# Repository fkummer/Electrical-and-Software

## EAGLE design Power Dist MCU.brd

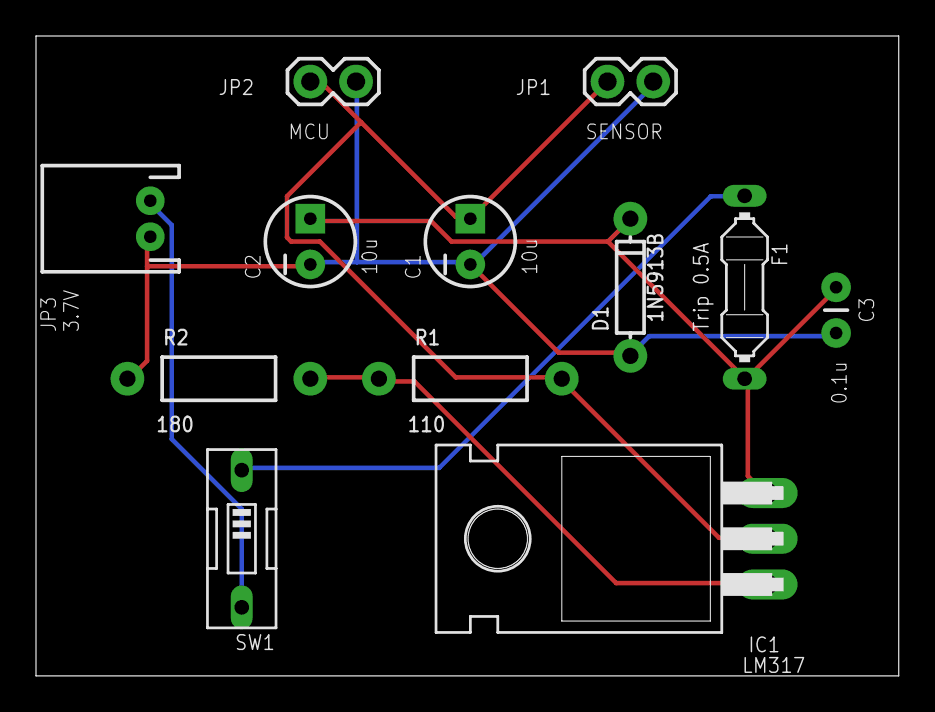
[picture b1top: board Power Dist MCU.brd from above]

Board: 2 copper layers, 47.9 x 35.5 mm, 12 parts (0 on the bottom side), 6 nets.

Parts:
C1, C2: 10u; CPOL-RADIAL-10UF-25V
C3: 0.1u; CAP-PTH-SMALL
D1: 1N5913B; DIODE-BZT52
F1: Trip 0.5A; PICOFUSE
IC1: LM317; TO220H
JP1: SENSOR; 1X02
JP2: MCU; 1X02
JP3: 3.7V; JST-2-PTH
R1: 110; AXIAL-0.4
R2: 180; AXIAL-0.4
SW1: EDG-01

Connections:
GND: C1.2, C2.2, C3.2, D1.A, JP1.2, JP2.2, JP3.1, R2.P$1
unnamed: F1.1, SW1.1
unnamed: JP3.2, SW1.2
unnamed: IC1.1, R1.P$1, R2.P$2
unnamed: C2.1, C3.1, D1.C, F1.2, IC1.3
VOUT: C1.1, IC1.2, JP1.1, JP2.1, R1.P$2

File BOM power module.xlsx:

Part Name | Value | Quantity | Datasheet | Supplier | Notes
LM317 Voltage Regulator | 1.5A current MAX | 1 | http://cdn.sparkfun.com/datasheets/Components/General/LM317TG.pdf | https://www.sparkfun.com/products/527 | MCU
LM350 | 3A+ | 1 | http://www.ti.com/lit/ds/symlink/lm350a.pdf | https://www.arrow.com/en/products/lm350t/texas-instruments?g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 | Motor
TVS DIODE 5VWM 9.2VC DO204AC | 6.4V Breakdown | 1 | http://www.littelfuse.com/~/media/electronics/datasheets/tvs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 | http://www.digikey.com/product-detail/en/littelfuse-inc/SA5.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 | Motor
Lithium Ion Battery | 2000mAh 2C 3.7V | 1 | https://www.sparkfun.com/datasheets/Batteries/UnionBattery-2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 | https://www.sparkfun.com/products/8483 | MCU
LiPo Battery JST Connector | 450mAh 25C 7.4V | 1 | http://www.buddyrc.com/glacier-20c-450mah-2s-jst.html | http://www.buddyrc.com/glacier-20c-450mah-2s-jst.html | Motor
Zener Diode | 3.3V impedence | 1 | http://www.mouser.com/ProductDetail/ON-Semiconductor/1N5913B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 | http://www.mouser.com/ds/2/308/1N5913B-D-11179.pdf | MCU
PTC Fuse | 3A hold 6A trip | 1 | http://www.littelfuse.com/~/media/electronics/product_specif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 | http://www.digikey.com/product-detail/en/RXEF300/RXEF300HF-N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

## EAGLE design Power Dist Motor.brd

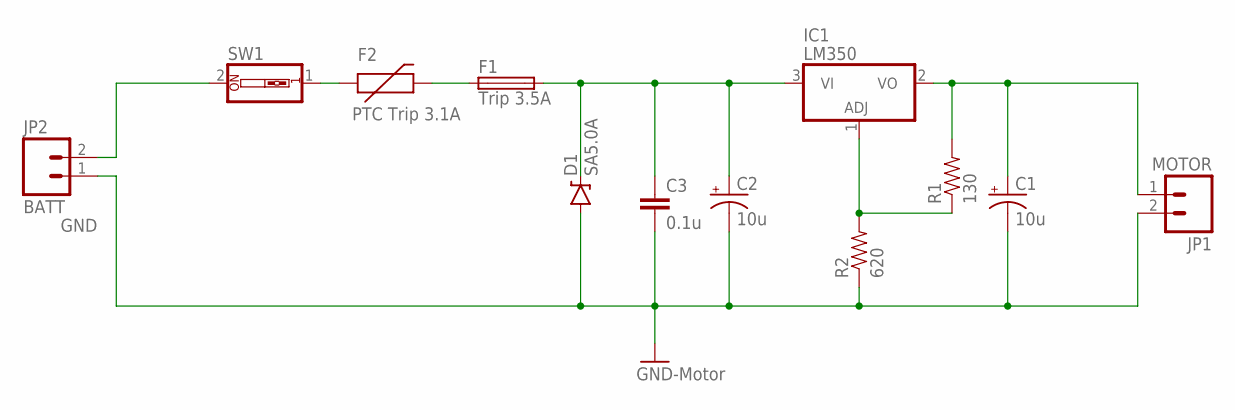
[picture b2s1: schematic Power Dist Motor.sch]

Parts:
C1, C2: 10u; CPOL-RADIAL-10UF-25V
C3: 0.1u; CAP-PTH-SMALL
D1: SA5.0A; DIODE-BZT52
F1: Trip 3.5A; PICOFUSE
F2: PTC Trip 3.1A; PTC
IC1: LM350; TO220H
JP1: MOTOR; 1X02
JP2: BATT; 1X02
R1: 130; AXIAL-0.4
R2: 620; AXIAL-0.4
SW1: SW_DIP-1; EDG-01

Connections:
GND: C1.2 (-), C2.2 (-), C3.2, D1.A, JP1.2, JP2.1, R2.P$1 (1)
unnamed: C1.1 (+), IC1.2 (VO), JP1.1, R1.P$2 (2)
unnamed: JP2.2, SW1.2
unnamed: F2.P$1 (1), SW1.1
unnamed: IC1.1 (ADJ), R1.P$1 (1), R2.P$2 (2)
unnamed: F1.1, F2.P$2 (2)
unnamed: C2.1 (+), C3.1, D1.C, F1.2, IC1.3 (VI)

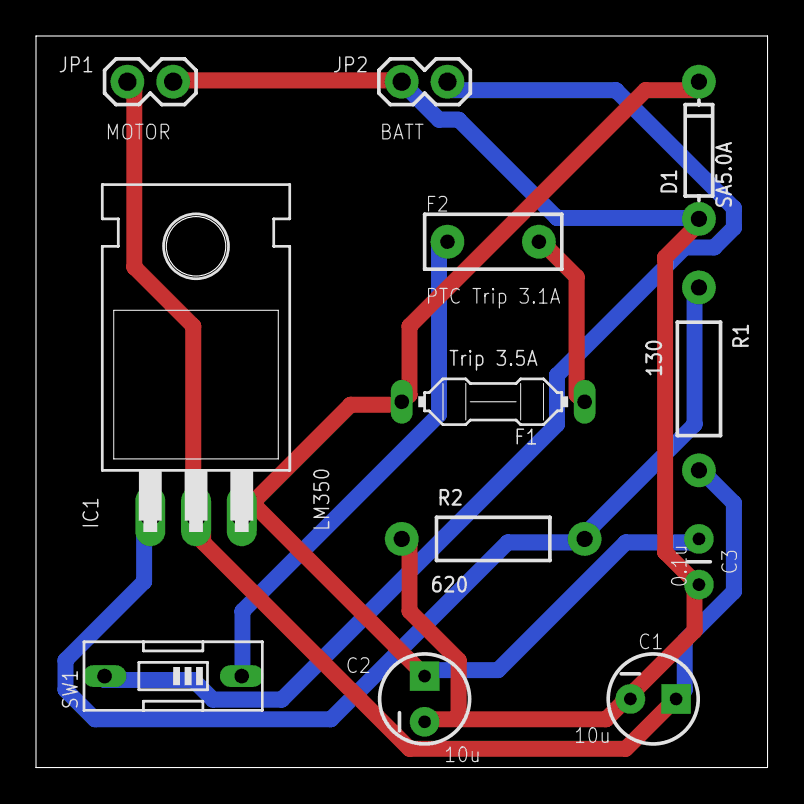
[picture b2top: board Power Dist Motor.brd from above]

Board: 2 copper layers, 40.6 x 40.6 mm, 12 parts (0 on the bottom side), 7 nets.

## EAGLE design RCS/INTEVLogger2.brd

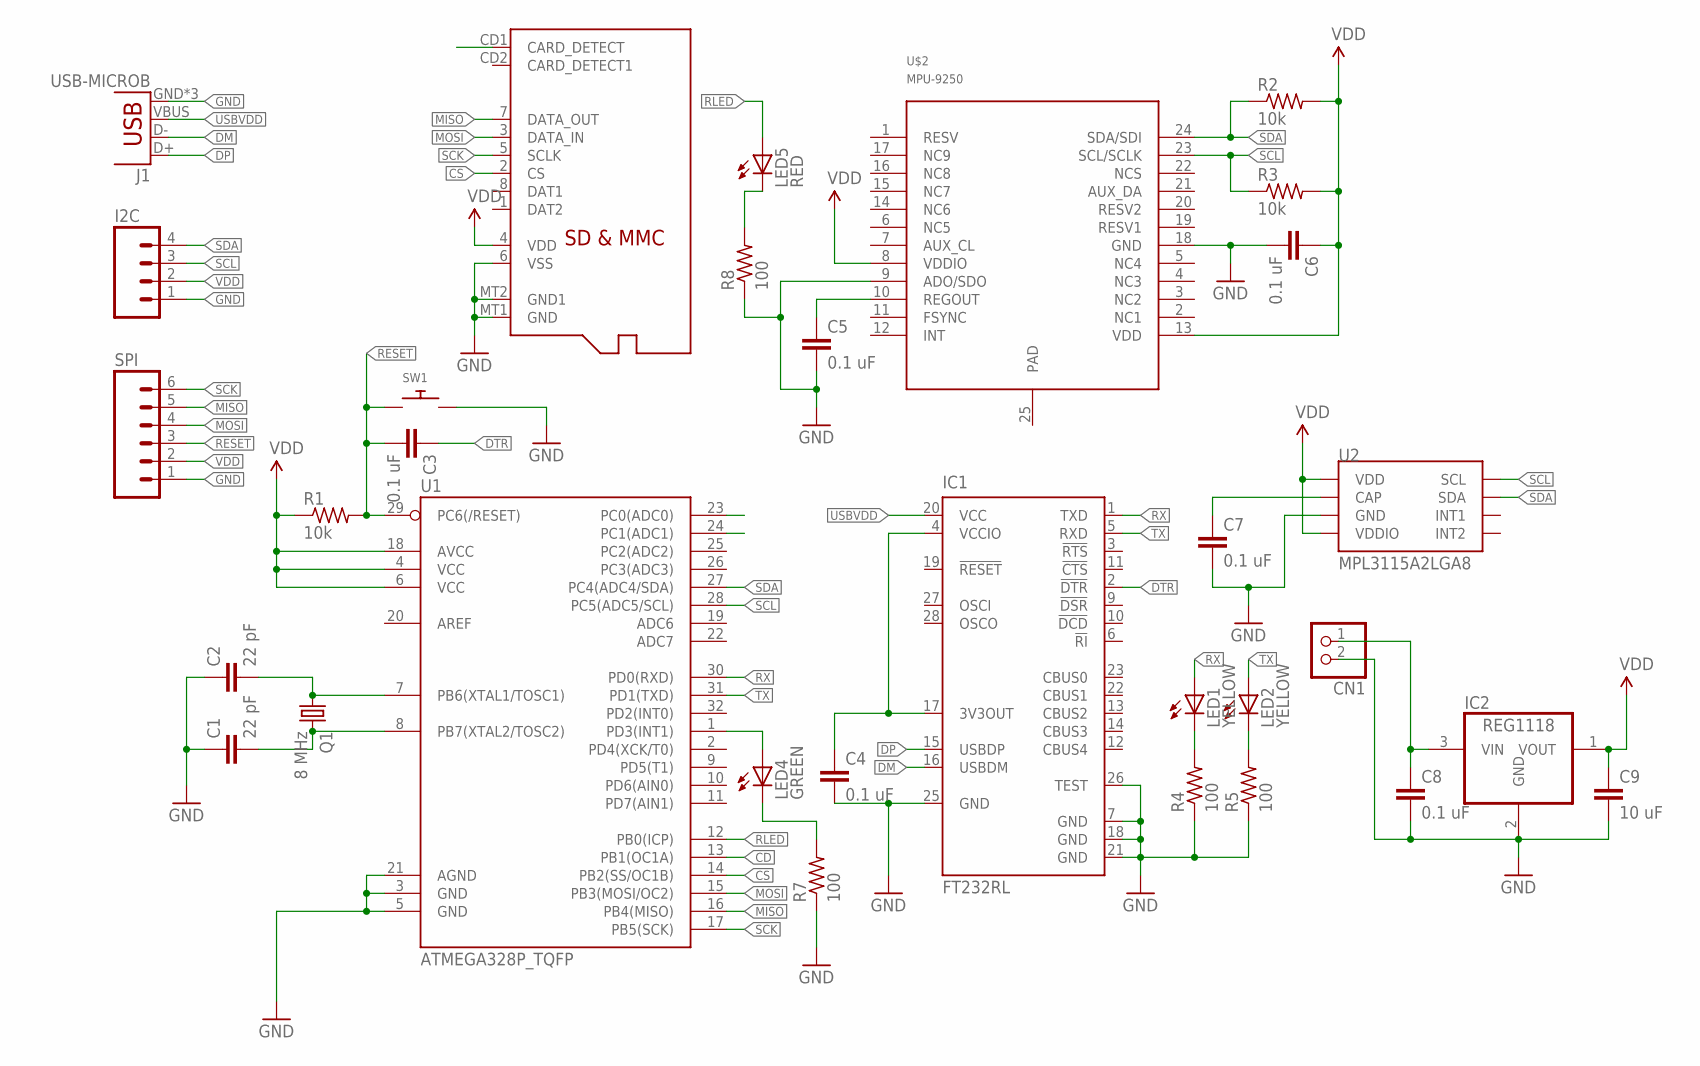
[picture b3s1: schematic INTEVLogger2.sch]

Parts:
C1, C2: 22 pF; 1206
C3, C4, C5, C6, C7, C8: 0.1 uF; 1206
C9: 10 uF; 1206
CN1: JST_2PIN-SMT; JST-PH-2-SMT
I2C: M04PTH; 1X04
IC1: FT232RL; SSOP28
IC2: REG1118; SOT223
J1: USB-MICROB
LED1, LED2: YELLOW; CHIPLED_1206
LED4: GREEN; CHIPLED_1206
LED5: RED; CHIPLED_1206
Q1: 8 MHz; HC49/S
R1, R2, R3: 10k; M1206
R4, R5, R7, R8: 100; M1206
SPI: M06LOCK; 1X06_LOCK
SW1: SWITCH_PUSHBUTTONSOFTTOUCHSMD_SJ; PUSHBUTTON_SMD_SJ
U1: ATMEGA328P_TQFP; TQFP32-08
U2: MPL3115A2LGA8; LGA8
U$1: MICROSD
U$2: MPU-9250; LEAD-QFN24

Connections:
CD: U1.13 (PB1(OC1A)), U$1.CD1 (CARD_DETECT)
CS: U1.14 (PB2(SS/OC1B)), U$1.2 (CS)
DM: IC1.16 (USBDM), J1.D-
DP: IC1.15 (USBDP), J1.D+
DTR: C3.1, IC1.2 (!DTR)
GND: C1.1, C2.1, C4.2, C5.2, C6.2, C7.2, C8.2, C9.2, CN1.2 (1), I2C.1, IC1.7 (GND), IC1.18 (GND), IC1.21 (GND), IC1.25 (GND), IC1.26 (TEST), IC2.2 (GND), J1.GND, J1.MT1 (GND), J1.MT2 (GND), R4.1, R5.1, R7.1, R8.1, SPI.1, SW1.P$2, U1.3 (GND), U1.5 (GND), U1.21 (AGND), U2.3 (GND), U$1.6 (VSS), U$1.MT1 (GND), U$1.MT2 (GND1), U$2.9 (ADO/SDO), U$2.18 (GND)
MISO: SPI.5, U1.16 (PB4(MISO)), U$1.7 (DATA_OUT)
MOSI: SPI.4, U1.15 (PB3(MOSI/OC2)), U$1.3 (DATA_IN)
unnamed: C1.2, Q1.2, U1.8 (PB7(XTAL2/TOSC2))
unnamed: C2.2, Q1.1, U1.7 (PB6(XTAL1/TOSC1))
unnamed: C5.1, U$2.10 (REGOUT)
unnamed: LED4.A, U1.1 (PD3(INT1))
unnamed: C8.1, CN1.1 (2), IC2.3 (VIN)
unnamed: C4.1, IC1.4 (VCCIO), IC1.17 (3V3OUT)
unnamed: C7.1, U2.2 (CAP)
unnamed: LED4.C, R7.2
unnamed: LED1.C, R4.2
unnamed: LED2.C, R5.2
unnamed: LED5.C, R8.2
RESET: C3.2, R1.2, SPI.3, SW1.P$1, U1.29 (PC6(/RESET))
RLED: LED5.A, U1.12 (PB0(ICP))
RX: IC1.1 (TXD), LED1.A, U1.30 (PD0(RXD))
SCK: SPI.6, U1.17 (PB5(SCK)), U$1.5 (SCLK)
SCL: I2C.3, R3.1, U1.28 (PC5(ADC5/SCL)), U2.8 (SCL), U$2.23 (SCL/SCLK)
SDA: I2C.4, R2.1, U1.27 (PC4(ADC4/SDA)), U2.7 (SDA), U$2.24 (SDA/SDI)
TX: IC1.5 (RXD), LED2.A, U1.31 (PD1(TXD))
USBVDD: IC1.20 (VCC), J1.VBUS
VDD: C6.1, C9.1, I2C.2, IC2.1 (VOUT), R1.1, R2.2, R3.2, SPI.2, U1.4 (VCC), U1.6 (VCC), U1.18 (AVCC), U2.1 (VDD), U2.4 (VDDIO), U$1.4 (VDD), U$2.8 (VDDIO), U$2.13 (VDD)

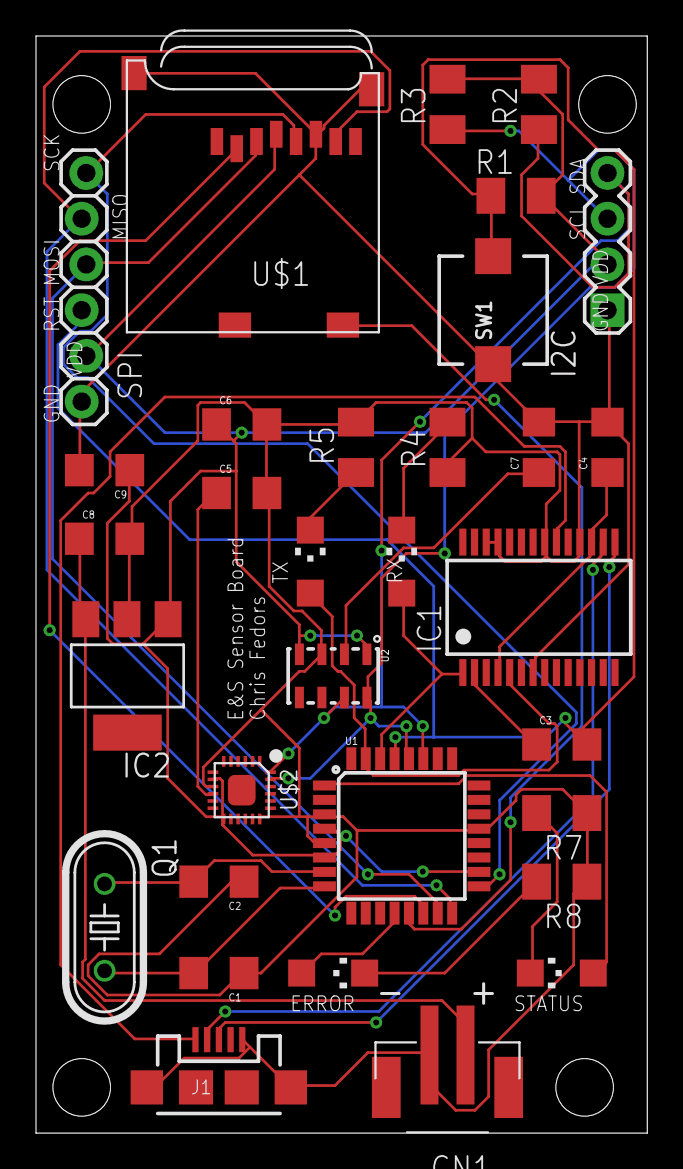
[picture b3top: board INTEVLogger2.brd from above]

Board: 2 copper layers, 34.0 x 61.0 mm, 32 parts (0 on the bottom side), 28 nets.

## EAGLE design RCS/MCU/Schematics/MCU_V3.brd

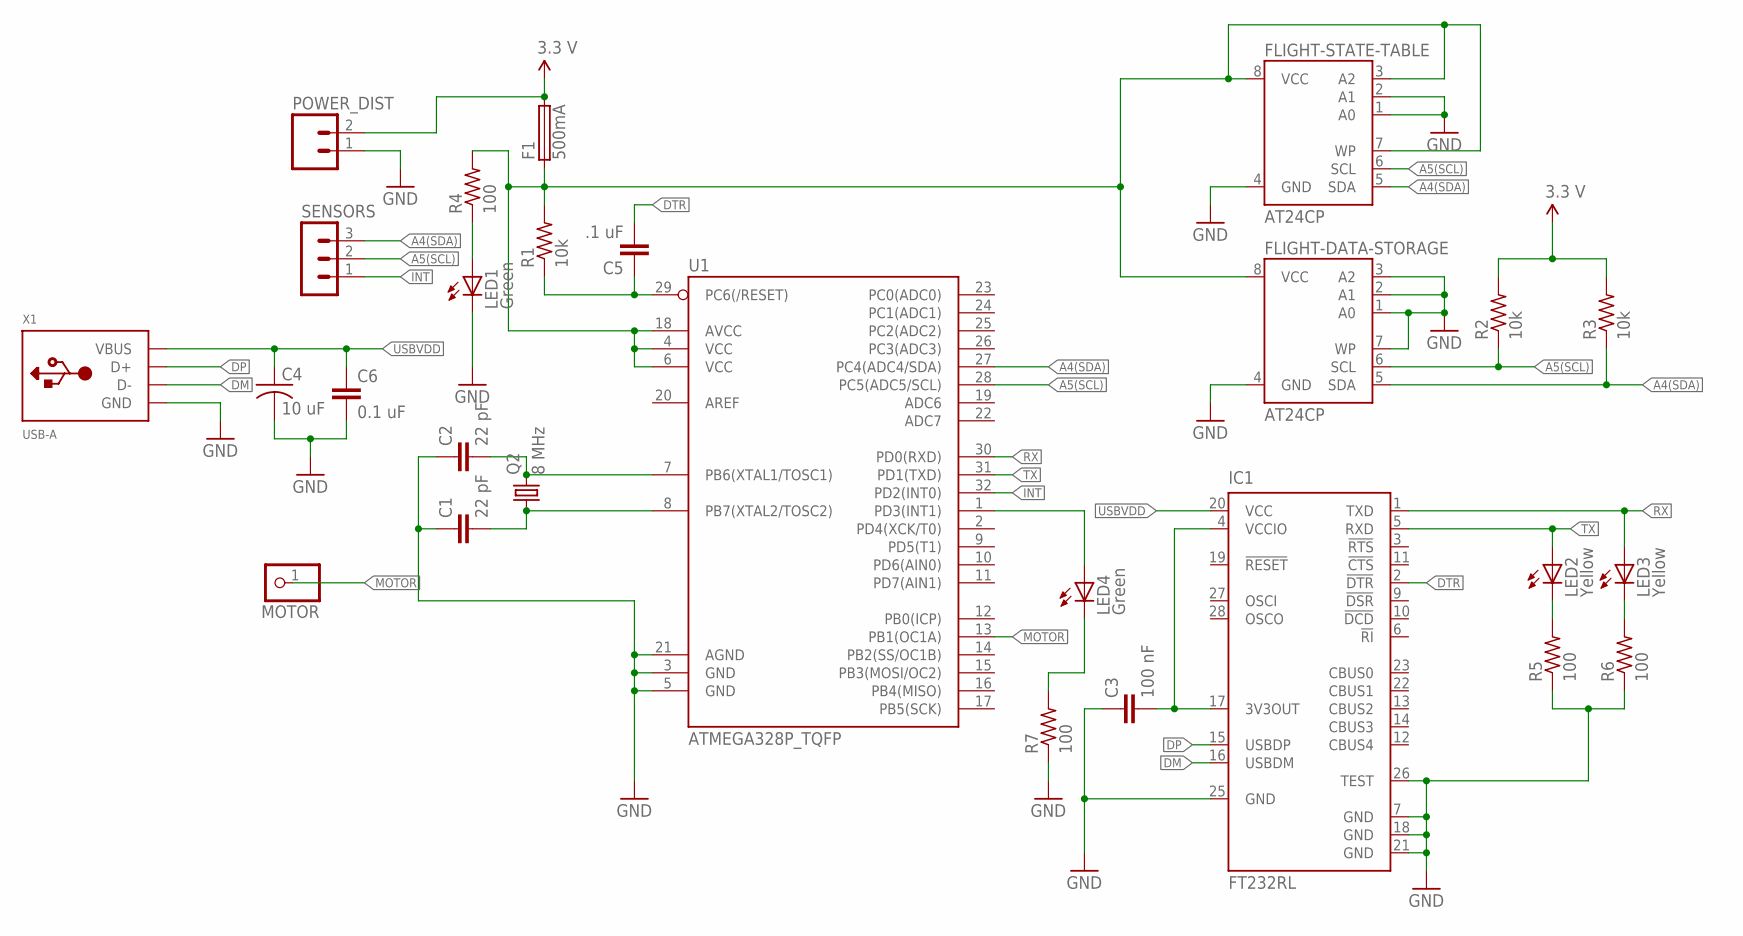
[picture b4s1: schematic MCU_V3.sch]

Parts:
C1, C2: 22 pF; C2.5-3
C3: 100 nF; C2.5-3
C4: 10 uF; C025-024X044
C5: .1 uF; C2.5-3
C6: 0.1 uF; C2.5-3
F1: 500mA; PICOFUSE
FLIGHT-DATA-STORAGE: AT24CP; DIL08
FLIGHT-STATE-TABLE: AT24CP; DIL08
IC1: FT232RL; SSOP28
LED1, LED4: Green; LED_SML0603
LED2, LED3: Yellow; LED_SML0603
MOTOR: PINHD-1X1; 1X01
POWER_DIST: M02PTH; 1X02
Q2: 8 MHz; HC49/S
R1, R2, R3: 10k; R0805
R4, R5, R6, R7: 100; R0805
SENSORS: MA03-1
U1: ATMEGA328P_TQFP; TQFP32-08
X1: USB-A; MOLEX_480371000

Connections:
A4(SDA): FLIGHT-DATA-STORAGE.5 (SDA), FLIGHT-STATE-TABLE.5 (SDA), R3.1, SENSORS.3, U1.27 (PC4(ADC4/SDA))
A5(SCL): FLIGHT-DATA-STORAGE.6 (SCL), FLIGHT-STATE-TABLE.6 (SCL), R2.1, SENSORS.2, U1.28 (PC5(ADC5/SCL))
DM: IC1.16 (USBDM), X1.2 (D-)
DP: IC1.15 (USBDP), X1.3 (D+)
DTR: C5.2, IC1.2 (!DTR)
GND: C1.1, C2.1, C3.1, C4.2, C6.2, FLIGHT-DATA-STORAGE.1 (A0), FLIGHT-DATA-STORAGE.2 (A1), FLIGHT-DATA-STORAGE.3 (A2), FLIGHT-DATA-STORAGE.4 (GND), FLIGHT-DATA-STORAGE.7 (WP), FLIGHT-STATE-TABLE.1 (A0), FLIGHT-STATE-TABLE.2 (A1), FLIGHT-STATE-TABLE.4 (GND), IC1.7 (GND), IC1.18 (GND), IC1.21 (GND), IC1.25 (GND), IC1.26 (TEST), LED1.C, POWER_DIST.1, R5.1, R6.1, R7.1, U1.3 (GND), U1.5 (GND), U1.21 (AGND), X1.4 (GND)
INT: SENSORS.1, U1.32 (PD2(INT0))
MOTOR: MOTOR.1, U1.13 (PB1(OC1A))
unnamed: C5.1, R1.1, U1.29 (PC6(/RESET))
unnamed: C2.2, Q2.2, U1.7 (PB6(XTAL1/TOSC1))
unnamed: C1.2, Q2.1, U1.8 (PB7(XTAL2/TOSC2))
unnamed: LED4.A, U1.1 (PD3(INT1))
unnamed: F1.1, FLIGHT-DATA-STORAGE.8 (VCC), FLIGHT-STATE-TABLE.3 (A2), FLIGHT-STATE-TABLE.7 (WP), FLIGHT-STATE-TABLE.8 (VCC), R1.2, R4.2, U1.4 (VCC), U1.6 (VCC), U1.18 (AVCC)
unnamed: LED1.A, R4.1
unnamed: C3.2, IC1.4 (VCCIO), IC1.17 (3V3OUT)
unnamed: LED4.C, R7.2
unnamed: LED2.C, R5.2
unnamed: LED3.C, R6.2
RX: IC1.1 (TXD), LED3.A, U1.30 (PD0(RXD))
TX: IC1.5 (RXD), LED2.A, U1.31 (PD1(TXD))
USBVDD: C4.1, C6.1, IC1.20 (VCC), X1.1 (VBUS)
VDD: F1.2, POWER_DIST.2, R2.2, R3.2

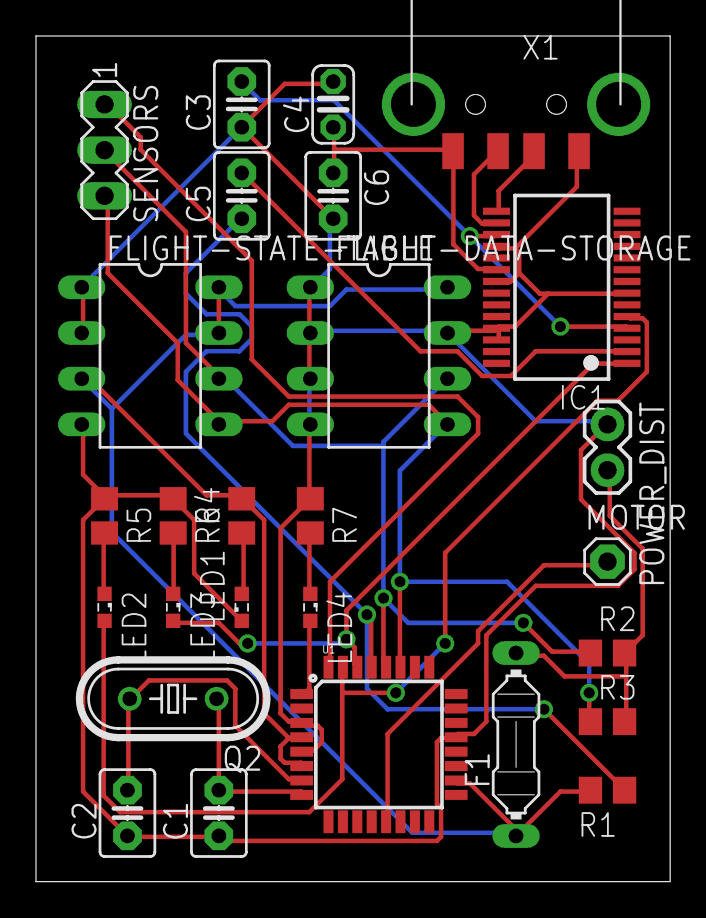
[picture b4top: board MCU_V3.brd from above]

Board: 2 copper layers, 35.2 x 47.0 mm, 27 parts (0 on the bottom side), 22 nets.

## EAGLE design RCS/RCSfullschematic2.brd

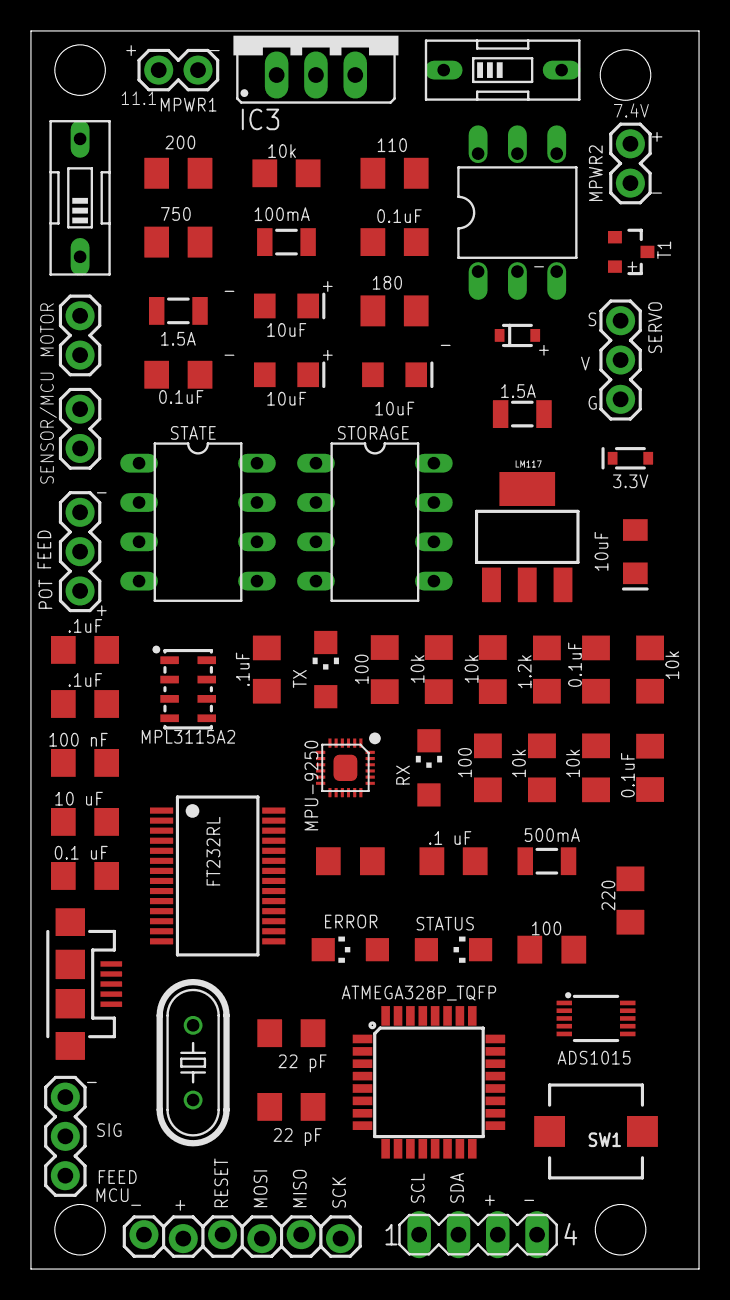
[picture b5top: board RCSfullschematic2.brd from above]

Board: 2 copper layers, 43.2 x 80.0 mm, 68 parts (0 on the bottom side), 45 nets, no tracks yet.

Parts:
C1, C2, C3: .1uF; 1206
C4, C5: 0.1uF; 1206
C6, C7: 22 pF; C1206
C8: 100 nF; C1206
C9: .1 uF; C1206
C10: 10 uF; C1206
C11: 0.1 uF; C1206
C12, C15: 0.1uF; C1206
C13, C14, C16, C17: 10uF; EIA3216
D1: 3.3V; SOD-323@2
D4: BAT20JFILM; SOD-323
ERROR: Red; CHIPLED_1206
F1, F4: 1.5A; PTC-1206
F2: 500mA; PTC-1206
F3: 100mA; PTC-1206
IC2: FT232RL; SSOP28
IC3: 317TS
J1: MA04-1
J6: 1X06_LOCK
J7: USB-MICROB
JP1: SENSOR/MCU; 1X02
JP5: MOTOR; 1X02
LM117: SOT223
MCU: 1X03
MPWR1: 11.1; 1X02
MPWR2: 7.4V; 1X02
OK1: 4N35; DIL06
POT: 1X03
Q2: 8 MHz; HC49/S
R1: 220; 1206
R2, R3: 10k; 1206
R4: 1.2k; 1206
R5, R6, R7, R11: 10k; R1206
R8, R9, R10, R16: 100; R1206
R12: 180; M1206
R13: 110; M1206
R14: 200; M1206
R15: 750; M1206
RX: Yellow; CHIPLED_1206
SERVO: SMALL_SERVO; 1X03
STATE: AT24CP; DIL08
STATUS: Green; CHIPLED_1206
STORAGE: AT24CP; DIL08
SW1: PUSHBUTTON_SMD_SJ
SW2, SW3: EDG-01
T1: MMBT2222A; SOT23-3
TX: Yellow; CHIPLED_1206
U1: MPL3115A2; LGA-8
U2: MPU-9250; LEAD-QFN24
U3: ATMEGA328P_TQFP; TQFP32-08
U4: ADS1015; MSOP10

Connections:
6V_POWER: C4.1, C5.1, D4.C, F1.1, R2.2, R3.1, SERVO.2
A4(SDA): J1.2, R7.1, STATE.5, STORAGE.5, U1.7, U2.24, U3.27, U4.9
A5(SCL): J1.1, R6.1, STATE.6, STORAGE.6, U1.8, U2.23, U3.28, U4.10
DM: IC2.16, J7.D-
DP: IC2.15, J7.D+
DTR: C9.2, IC2.2
FEEDBACK: MCU.1, POT.2, U3.26, U4.4
GND: C1.2, C2.2, C3.2, C6.1, C7.1, C8.1, C10.2, C11.2, C12.2, C13.-, C14.-, D1.A, IC2.7, IC2.18, IC2.21, IC2.25, IC2.26, J1.4, J6.1, J7.GND, J7.MT1, J7.MT2, JP1.2, MCU.3, MPWR2.1, OK1.2, R4.2, R8.1, R9.1, R10.1, R11.2, R12.1, R16.1, STATE.1, STATE.2, STATE.4, STORAGE.1, STORAGE.2, STORAGE.3, STORAGE.4, STORAGE.7, SW1.P$2, U1.3, U2.9, U2.11, U2.18, U2.20, U3.3, U3.5, U3.21, U4.3
GND1: C4.2, C5.2, C15.2, C16.-, C17.-, D4.A, JP5.2, MPWR1.1, OK1.4, R15.1, SERVO.3, T1.2
INT: U2.12, U3.32
LOGIC_VDD: C3.1, C14.+, D1.C, F2.2, J1.3, JP1.1, LM117.2, POT.1, R6.2, R7.2, R13.2, U1.1, U1.4, U2.1, U2.8, U2.13, U2.19
MISO: J6.5, U3.16
MOSI: J6.4, U3.15
MOTOR: MCU.2, R1.1, U3.13
unnamed: C1.1, U1.2
unnamed: OK1.5, R2.1, T1.1
unnamed: C2.1, U2.10
unnamed: POT.3, R4.1
unnamed: R11.1, U4.1
unnamed: OK1.1, R1.2
unnamed: C7.2, Q2.2, U3.7
unnamed: C6.2, Q2.1, U3.8
unnamed: R8.2, TX.C
unnamed: R9.2, RX.C
unnamed: STATUS.A, U3.1
unnamed: R10.2, STATUS.C
unnamed: ERROR.C, R16.2
unnamed: LM117.1, R12.2, R13.1
unnamed: MPWR2.2, SW2.2
unnamed: C12.1, C13.+, F3.2, LM117.3
unnamed: F3.1, SW2.1
unnamed: MPWR1.2, SW3.2
unnamed: F4.1, SW3.1
unnamed: C15.1, C16.+, F4.2, IC3.3
unnamed: IC3.1, R14.1, R15.2
unnamed: ERROR.A, U3.2
RESET: C9.1, J6.3, R5.1, SW1.P$1, U3.29
RX: IC2.1, RX.A, U3.30
SCK: J6.6, U3.17
SIGNAL: R3.2, SERVO.1, T1.3
TX: IC2.5, TX.A, U3.31
USBVDD: C10.1, C11.1, IC2.20, J7.VBUS
VCC: F2.1, R5.2, STATE.3, STATE.7, STATE.8, STORAGE.8, U3.4, U3.6, U3.18, U3.20, U4.8
VDD_IO: C8.2, IC2.4, IC2.17
VOUT-MOTOR: C17.+, F1.2, IC3.2, JP5.1, R14.2

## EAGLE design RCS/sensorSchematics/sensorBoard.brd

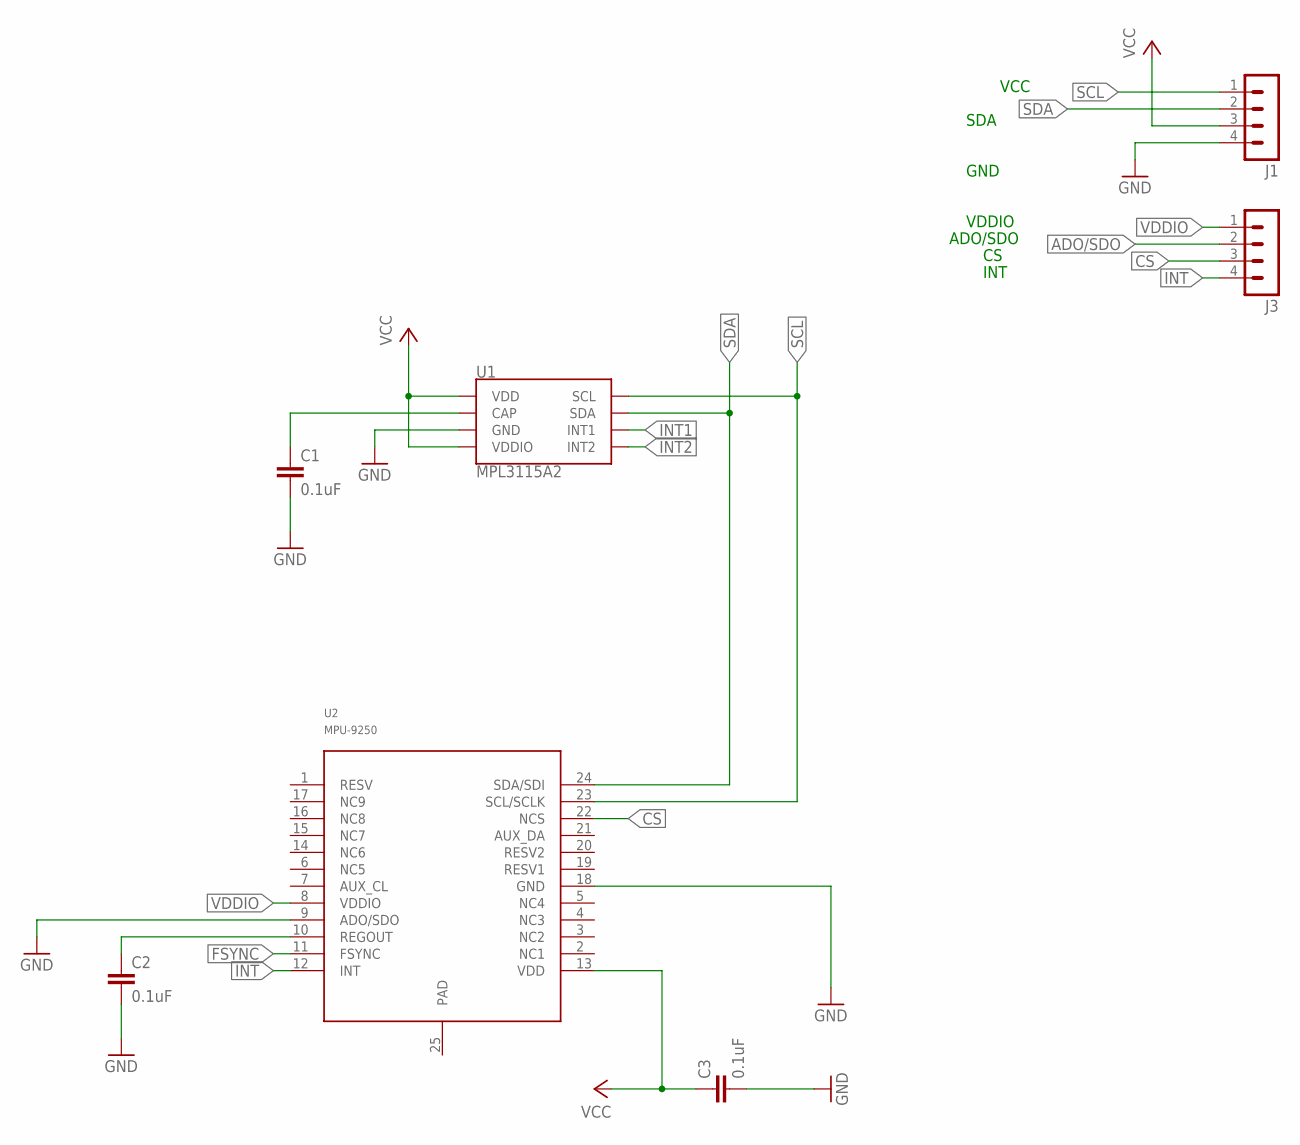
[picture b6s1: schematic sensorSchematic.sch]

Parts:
C1, C2, C3: 0.1uF; 0402
J1, J3: MA04-1
U1: MPL3115A2; LGA-8
U2: MPU-9250; LEAD-QFN24

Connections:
ADO/SDO: J3.2
CS: J3.3, U2.22 (NCS)
FSYNC: U2.11 (FSYNC)
GND: C1.2, C2.2, C3.2, J1.4, U1.3 (GND), U2.9 (ADO/SDO), U2.18 (GND)
INT: J3.4, U2.12 (INT)
INT1: U1.6 (INT1)
INT2: U1.5 (INT2)
unnamed: C1.1, U1.2 (CAP)
unnamed: C2.1, U2.10 (REGOUT)
SCL: J1.1, U1.8 (SCL), U2.23 (SCL/SCLK)
SDA: J1.2, U1.7 (SDA), U2.24 (SDA/SDI)
VCC: C3.1, J1.3, U1.1 (VDD), U1.4 (VDDIO), U2.13 (VDD)
VDDIO: J3.1, U2.8 (VDDIO)

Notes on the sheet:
VCC
SDA
GND
VDDIO
ADO/SDO
INT

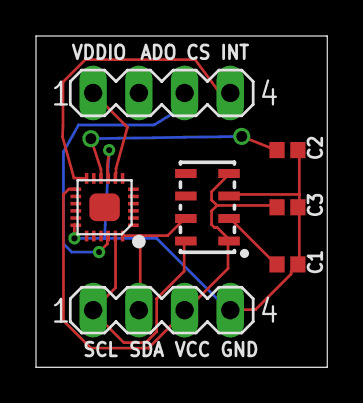
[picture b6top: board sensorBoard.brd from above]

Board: 2 copper layers, 16.2 x 18.4 mm, 7 parts (0 on the bottom side), 9 nets.

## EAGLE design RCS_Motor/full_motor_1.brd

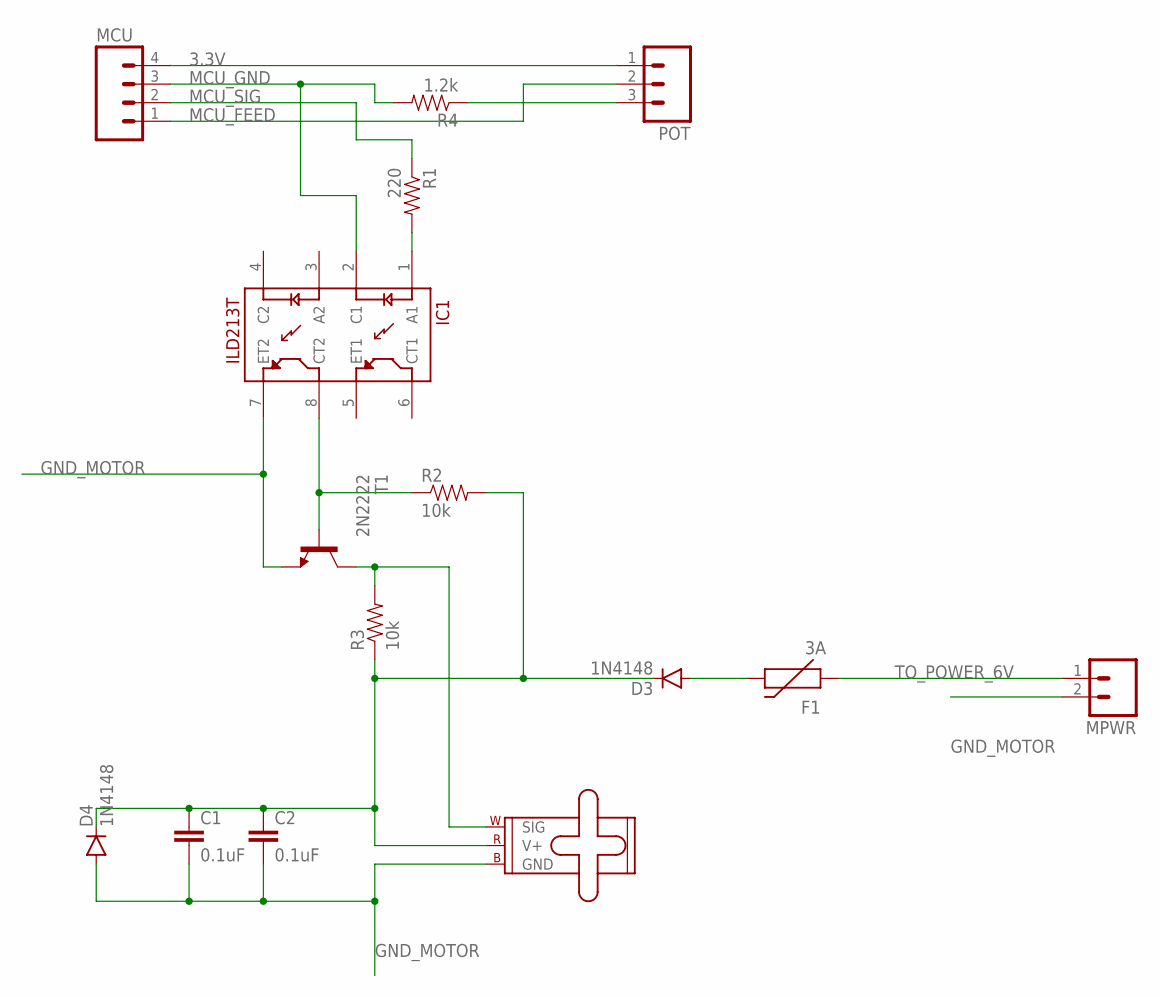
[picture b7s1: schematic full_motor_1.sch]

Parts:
C1, C2: 0.1uF; 1206
D3, D4: 1N4148; DIODE-1N4148
F1: 3A; PTC-1206
IC1: ILD213T; SO08
MCU: M04PTH; 1X04
MPWR: M02PTH; 1X02
POT: M03PTH; 1X03
R1: 220; 1206
R2, R3: 10k; 1206
R4: 1.2k; 1206
SERVO: SMALL_SERVO; 1X03
T1: 2N2222; TO92-EBC-OVAL

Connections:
3.3V: MCU.4, POT.1
6V_POWER: C1.1, C2.1, D3.C, D4.C, R2.2, R3.1, SERVO.2 (V+)
GND_MOTOR: C1.2, C2.2, D4.A, IC1.7 (ET2), MPWR.2, SERVO.3 (GND), T1.E
MCU_FEED: MCU.1, POT.2
MCU_GND: IC1.2 (C1), MCU.3, R4.2
MCU_SIG: MCU.2, R1.1
unnamed: IC1.1 (A1), R1.2
unnamed: POT.3, R4.1
unnamed: IC1.8 (CT2), R2.1, T1.B
unnamed: D3.A, F1.2
unnamed: R3.2, SERVO.1 (SIG), T1.C
TO_POWER_6V: F1.1, MPWR.1

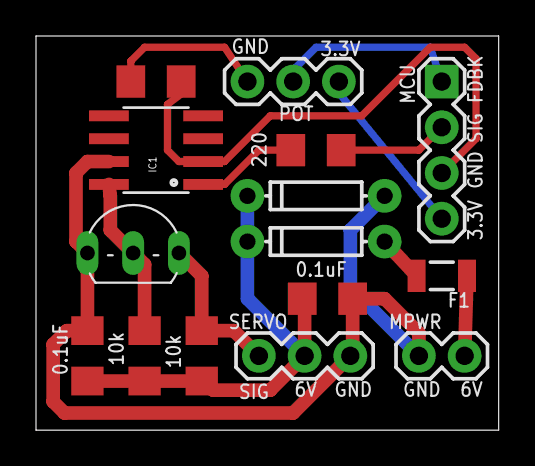
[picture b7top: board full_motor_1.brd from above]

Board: 2 copper layers, 25.7 x 21.9 mm, 15 parts (0 on the bottom side), 12 nets.

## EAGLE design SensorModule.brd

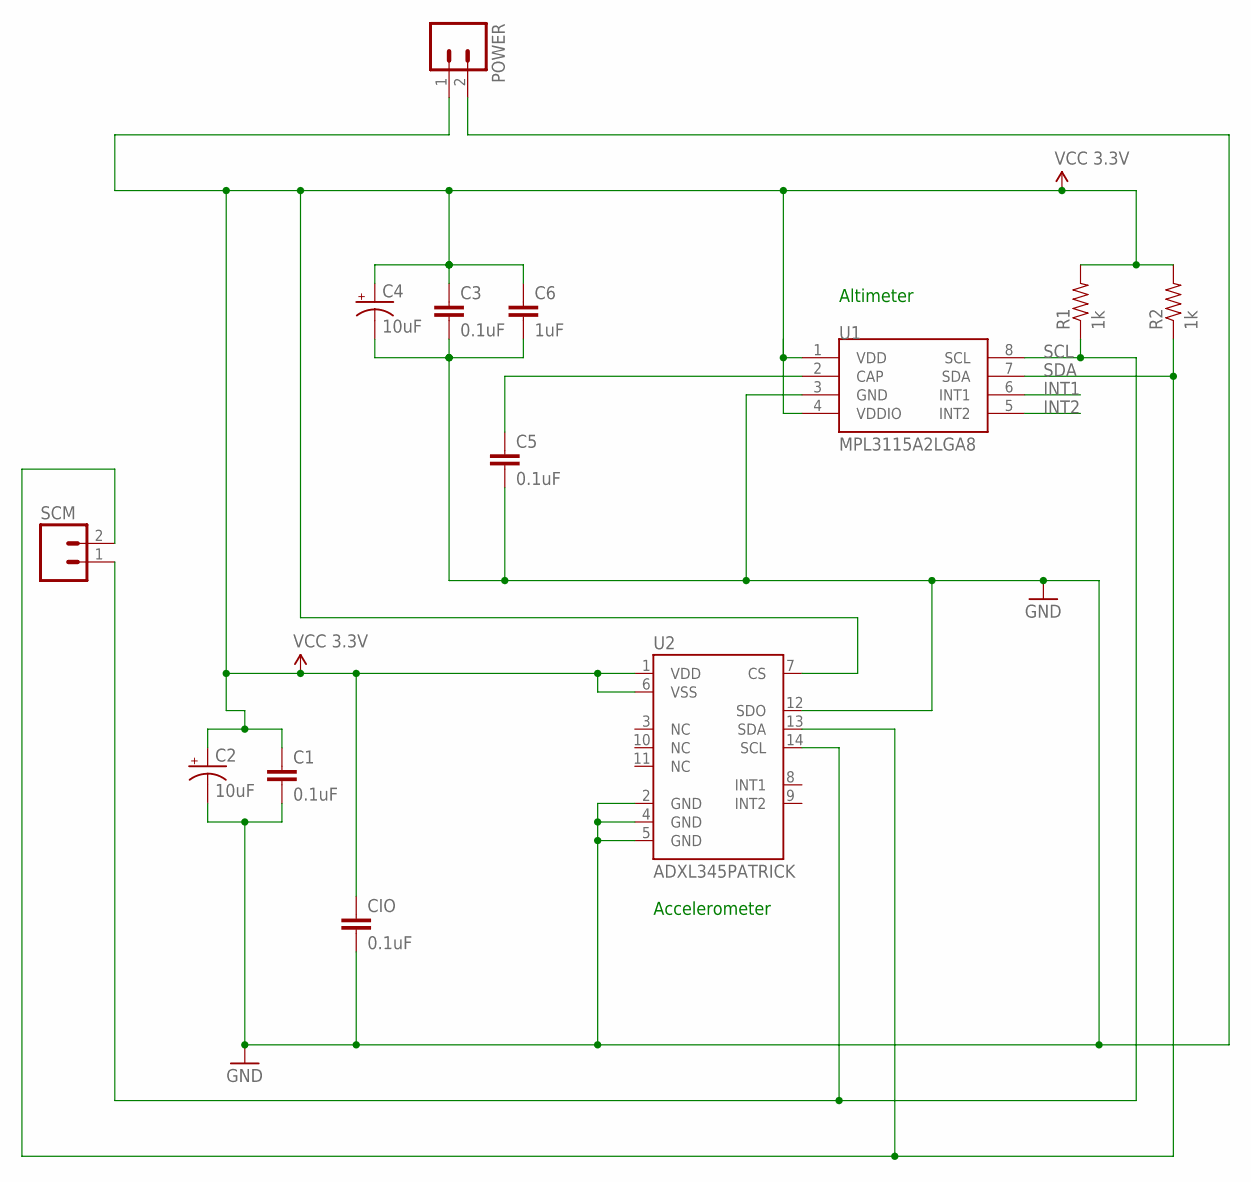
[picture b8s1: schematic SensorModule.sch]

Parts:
C1, C3, C5: 0.1uF; CAP-PTH-SMALL
C2, C4: 10uF; CPOL-RADIAL-10UF-25V
C6: 1uF; CAP-PTH-SMALL
CIO: 0.1uF; CAP-PTH-SMALL
POWER: M02PTH; 1X02
R1, R2: 1k; AXIAL-0.4
SCM: M02PTH; 1X02
U1: MPL3115A2LGA8; LGA8
U2: ADXL345PATRICK; LGA14_1:1_PATRICK

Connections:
GND: C1.2, C2.2 (-), C3.2, C4.2 (-), C5.2, C6.2, CIO.2, POWER.2, U1.3 (GND), U2.2 (GND), U2.4 (GND), U2.5 (GND), U2.12 (SDO)
INT1: U1.6 (INT1)
INT2: U1.5 (INT2)
unnamed: C5.1, U1.2 (CAP)
SCL: R1.P$1 (1), SCM.1, U1.8 (SCL), U2.14 (SCL)
SDA: R2.P$1 (1), SCM.2, U1.7 (SDA), U2.13 (SDA)
VCC_3.3V: C1.1, C2.1 (+), C3.1, C4.1 (+), C6.1, CIO.1, POWER.1, R1.P$2 (2), R2.P$2 (2), U1.1 (VDD), U1.4 (VDDIO), U2.1 (VDD), U2.6 (VSS), U2.7 (CS)

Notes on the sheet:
Altimeter
Accelerometer

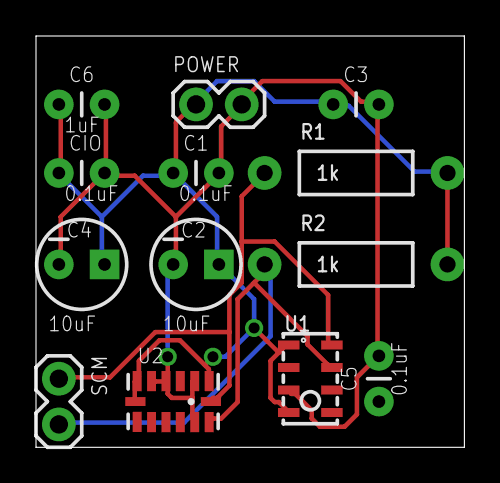
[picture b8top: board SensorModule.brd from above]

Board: 2 copper layers, 23.8 x 22.9 mm, 13 parts (0 on the bottom side), 5 nets.

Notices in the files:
parts and their libraries:
SparkFun-Capacitors: Licensing: Creative Commons ShareAlike 4.0 International - https://creativecommons.org/licenses/by-sa/4.0
SparkFun-Sensors: Licensing: CC v3.0 Share-Alike You are welcome to use this library for commercial purposes.
